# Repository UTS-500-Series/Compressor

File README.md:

# UTS Mini Mixing Desk — Compressor

A 500-series compressor module for the UTS Mini Mixing Desk. Feedback topology, discrete
current-steering gain cell, balanced in and out, running on the rack's ±16 V.

Built from ordinary parts: **nine BC549 transistors and seven NE5532 op amps**, plus a
pair of LM391x bargraph drivers for the meters. No VCA chip,
no transformers, nothing hard to source.

📖 **Documentation: [uts-500-series.github.io/compressor](https://uts-500-series.github.io/compressor/)** — every section explained, with
interactive schematics you can click through, plus the routed boards and their design files.
The site's source is a separate repository, [UTS-500-Series.github.io](https://github.com/UTS-500-Series/UTS-500-Series.github.io).

---

## Status

| | |
|---|---|
| Schematic | Complete, 7 sheets |
| Components | 166 |
| Nets | 110 |
| ERC | 0 errors, 0 warnings |
| PCB layout | Main board and front board placed and routed, DRC clean. Main board re-routed with paired audio lines and an unbroken ground pour; front board still as autorouted |
| Simulated | Yes, in ngspice from the `kicad/` sheets. See [kicad/sim](kicad/sim/README.md) |
| Built | No |

**Every performance figure in the documentation is calculated from the design, not measured.**
The netlist has been verified and ERC is clean, but that only proves the drawing is
self-consistent — not that the circuit behaves as predicted. The [simulation](kicad/sim/README.md)
checks the behaviour with models of the real parts, and found a few places where it differs
from the documentation.

## Repository layout

```
kicad_withpcb/compressor_with_pcb/   the main board: flat schematic + routed PCB (KiCad 10)
kicad_withpcb/compressor_front/      the front board behind the panel: schematic + routed PCB
kicad/                               the original seven-sheet schematic (KiCad 9), used by the site
tools/                               design.py (the reference netlist) and the check/build scripts
panel/                               faceplate generator — mockups, a 1:1 drawing and a DXF
```

**The boards are built from `kicad_withpcb/`.** The flat schematic there drives the main
board's PCB, and the front board has its own schematic joined to it by a 30-way ribbon.
`tools/design.py` is the reference netlist. Compare the flat schematic against it after any
wiring edit: KiCad's DRC parity check only compares the PCB with the flat schematic, so it
can't see a wiring mistake in the schematic itself.

The seven-sheet `kicad/` project is the original drawing of the same circuit. It has no PCB,
but the documentation site's interactive schematics are built from it. The site lives in its
own repository, [UTS-500-Series.github.io](https://github.com/UTS-500-Series/UTS-500-Series.github.io),
because it covers the whole desk rather than this module.

## Opening it

The boards need **KiCad 10**:

- `kicad_withpcb/compressor_with_pcb/compressor_with_pcb.kicad_pro`: the main board, the
  500-series card (152.35 × 105 mm) with the edge connector.
- `kicad_withpcb/compressor_front/compressor_front.kicad_pro`: the 35 × 110 mm front board
  with the pots, toggles and meters. Its [README](kicad_withpcb/compressor_front/README.md)
  covers how it mounts, the ribbon, the bracket and what to check before ordering.

Run `sh tools/get_3d_models.sh` once after cloning. It fetches Alps' RK09K pot model, which
isn't kept in git, so the 3D viewer and STEP export show the pots.

The original schematic is `kicad/UTS Mini Mixing Desk - Compressor.kicad_pro` (**KiCad 9**). Its root sheet holds seven
sub-sheets:

| Sheet | What it covers |
|---|---|
| 1 Connector | The 500-series edge connector |
| 2 Input | Balanced receiver and the input pad |
| 3 VCA | The current-steering gain cell and recovery amplifier |
| 4 Output | Makeup gain, output drivers, bypass, aux section |
| 5 Sidechain | Detector: threshold, rectifier, ratio, attack/release |
| 6 Power | Rails, references, bias, grounding, decoupling |
| 7 Meters | Gain-reduction and output-level LED bargraphs |

Only stock KiCad symbol and footprint libraries are used, so there is nothing to install.

## How it works, in one paragraph

A compressor needs a gain it can change electrically, and a way to measure loudness. The gain
cell here keeps a **fixed 3 mA tail current** through a matched BC549 pair and varies gain by
*steering* that current between an output load and the supply rail, rather than by varying the
current itself. That costs four extra transistors and buys a distortion figure that stays flat
at every amount of gain reduction — the simpler tail-current approach distorts worst exactly
when it is compressing hardest. The detector listens to the module's own **output**, making
this a feedback compressor: the ratio emerges from loop gain rather than being dialled in, the
knee comes out soft on its own, and the circuit is forgiving of component tolerance.

The [documentation](../UTS-500-Series.github.io) covers all of this properly, section by section.

## Specifications

| | |
|---|---|
| Format | 500 series, 15-pin EDAC card edge |
| Supply | ±16 V from the rack, 72 / 62 mA at rest (simulated) |
| Input | Balanced, 44 kΩ differential, +4 dBu nominal |
| Output | Balanced, 100 Ω build-out per leg |
| Gain reduction | 36 dB maximum (simulated) |
| Attack | 2 – 71 ms (simulated) |
| Release | 49 ms – 3.5 s (simulated) |
| Controls | Threshold, Ratio, Attack, Release, Makeup |
| Switches | Bypass, sidechain key int/ext, sidechain HPF, stereo link |

## Front panel

[`panel/`](panel/) holds the faceplate: a mockup, a dimensioned 1:1 drawing, and a DXF of the
outline and holes for a panel shop. All three are generated from one definition by
`panel/make_panel.py`, which runs a clearance check on every build.

Panel is the standard 500-series 1.500″ × 5.250″ × 0.125″ with two countersunk mounting holes
125.43 mm apart, badged **OPN-500 / CMP-01**.

The default layout, and the one the front board is built for, is **`toggle`**: five single
9 mm pots (THRESHOLD, RATIO, ATTACK, RELEASE, MAKEUP), four mini toggles (HPF and KEY
either side of THRESHOLD, LINK and BYPASS either side of RATIO), and two 10-LED meters for
gain reduction and output level. That's 31 holes, and `make_panel.py` takes their
positions from the front board. The toggles are Salecom mini toggles from Altronics:
S1350 (DPDT) for BYPASS and S1315 (SPDT) for KEY, HPF and LINK, in 6.5 mm holes for their
1/4-40 bushings. The S1332 (SPDT centre-off) fits the same footprint if a three-position
switch is ever wanted.

The toggles' 8.9 mm bushing leaves about 5.5 mm of thread through a 3.18 mm panel, so they
are no longer the tight spot. The 9 mm pots are: their 5 mm bushing leaves under 2 mm for
the nut, so thin the panel to about 2 mm around the five pot holes, or use a thinner panel.

`make_panel.py` also keeps a `pull` layout (every switch on a pull-switch pot) and a
`concentric` layout (dual-concentric knobs and a lit BYPASS button), plus a `bone` finish
alongside the default dark anodised one. The boards are only drawn for `toggle`. See
[`panel/README.md`](panel/README.md).

No laser cutter or CNC? [`panel/print/`](panel/print/README.md) has a 3D-printable faceplate
(STL and OpenSCAD) with the same holes, a flat front at the pots, meter holes sized for the
Jaycar 2 mm tower LEDs, an engraved legend that can print in a second colour, and a
fit-test strip to print first. It also comes
as a STEP file (`faceplate.step`) for Fusion or any other CAD program, plus a STEP with no
legend and the legend as a DXF, for laying out your own.

## Bill of materials

**[`bom/altronics.csv`](bom/altronics.csv)** is the order list for both boards from Altronics,
with catalogue codes, a link to each product page, pack sizes, prices and the stock their
site showed on the day it was checked. `python3 tools/bom_altronics.py` rebuilds it from the two `kicad_withpcb`
schematics, so it follows the boards rather than `design.py`; a part drawn on both sheets
is counted once, on the front board. It includes the hardware the schematics don't: DIP-8
sockets for U1–U7, knobs, the board-to-board ribbon and M3 screws for the bracket. The
two LM3914 meter drivers are soldered straight in, because sockets would overlap the
meter LEDs.

Altronics doesn't stock everything. The script lists those lines with another supplier:
the 2.2–10 µF film capacitors, R61/R62 at 0.1%, and the twenty 2 mm meter LEDs (Altronics'
3 mm flangeless LEDs don't fit the meters' 3.0 mm pitch). The main board is drawn for these
film capacitors: TDK B32562H1106K000 (10 µF, C5, C8, C15) and
B32562H1475K000 (4.7 µF, C9, C10), both 15 mm pitch, and KEMET MMK5225K63J06L4BULK
(2.2 µF, C14, C35) on 5 mm. RV5 (ATTACK) is 10k and RV6 (RELEASE) 1M, Altronics' nearest
9 mm values.

**[`bom/ordered.csv`](bom/ordered.csv)** is what was actually bought for the first build,
split between Altronics, DigiKey and Jaycar, with the supplier, order code, part, quantity and
link for every reference on both boards.

- **Altronics:** the pots, toggles, knobs, trimpots, sockets, headers, ribbon, small ceramics,
  electrolytics, 1N4148/1N4004 diodes, the GR LED and R37, R42 and R44.
- **DigiKey:** the 10 µF and 4.7 µF film capacitors (C5, C8, C15, C9, C10), R61/R62 at 0.1%,
  the NE5532s, the BC549Cs, the BZX79 zener, the 100 nF ceramics and the 22 µF bipolars (C1, C2).
- **Jaycar:** every other resistor (0.5 W mini metal film, which fits the 0.25 W outline), the
  TL072, both LM3914s, the twenty meter LEDs and C14/C35.

Three substitutions differ from the drawing. The meter LEDs are Jaycar 2 mm tower LEDs, orange
in the amber positions. C14 and C35 are 2.2 µF bipolar electrolytics (Jaycar RY6804), because
the 2.2 µF film part was out of stock everywhere we looked; neither is in the audio path. C1/C2 are
Panasonic ECE-A1VN220U (35 V, the 50 V parts don't fit the 6.3 mm outline). The bracket
hardware wasn't in any order.

The output-level meter was an LM3915, whose ten steps are 3 dB apart. Nobody stocks it any
more, so U10 is now an LM3914 like the gain-reduction meter, and both meters have ten LEDs on
a 3.0 mm pitch (they had seven on 3.5 mm). R92 is 4k7, so RV8 can set the top level LED at
+18 dBu. The LM3914's steps are even in volts, so the level LEDs light at about −2, +4, +7.5,
+10, +12, +13.6, +15, +16, +17 and +18 dBu: a 20 dB span with the finest steps near
clipping. With RV7 set for a 30 dB top LED, the gain-reduction LEDs light at about 2, 3, 5,
7, 10, 13, 17, 21, 26 and 30 dB. Both scales are simulated: see
[kicad/sim/README.md](kicad/sim/README.md#the-meters).
`tools/bom_order.py` is the older DigiKey list, built from `design.py`.

The circuit itself is 172 components across 58 distinct line items: 73 resistors, 39 capacitors, 21 LEDs,
9 transistors, 8 potentiometers, 8 diodes, 7 op amps, 4 switches, 2 display drivers,
1 connector.

Four things are not substitutable:

- **Q1/Q2 must be a matched pair, and Q6–Q9 a matched quad**, all glued together so they stay
  at the same temperature. The steering balance is set by base-emitter voltages differing by
  tens of millivolts, and those drift ~2 mV per °C.
- **R1–R4 and R21–R24 want 0.1%.** R1–R4 set input common-mode rejection; R21–R24 set how well
  the recovery amp rejects the gain cell's step, which is audible as thump on fast attacks.
- **R61 (1k33) and R62 (23k2) want 0.1%.** They set the gain cell's resting point.
- **C15 must be film.** An electrolytic's leakage is in the same league as the release current
  at long settings and will shorten your slowest release.

One recommended deviation: fit a **TL072 or OPA2134 for U4** instead of an NE5532. Its inputs
sit on the timing capacitor, and the NE5532's ~200 nA bias current can leave the compressor
holding about a decibel of gain reduction at idle. Pin compatible, nothing else changes.

## Ordering the boards

Each board's fab files are in its `Gerbs/` folder, zipped ready to upload:
`kicad_withpcb/compressor_with_pcb/Gerbs/compressor_with_pcb-gerbers.zip` (main board,
128.4 × 105.05 mm including the edge-connector tab) and
`kicad_withpcb/compressor_front/Gerbs/compressor_front-gerbers.zip` (front board, 35 × 110 mm).
Both are 2-layer, 1.6 mm FR-4, 1 oz copper, through-hole only (no paste layers). Smallest
track 0.2 mm, clearance 0.2 mm, drill 0.4 mm, so any standard fab process takes them.

The main board's edge fingers plug into the rack, so ask for gold fingers with a 30–45° bevel
if the fab offers it. Plain HASL works for a prototype but wears with repeated insertion.

**Re-plot after every board change**, so the zips never lag the board:

```bash
sh tools/plot_fab.sh                 # both boards, needs KiCad 10's kicad-cli
```

## Calibrating the meters

`tools/calibrate_meters.py` sets RV8 (level) and RV7 (gain reduction) with an audio interface,
a loopback cable and a multimeter. It learns the interface's levels in dBu, then holds a tone
at each meter's target while you turn the trimpot, and can sweep each meter afterwards to check
every LED against the simulated scale in [kicad/sim/README.md](kicad/sim/README.md#the-meters).

```bash
python3 -m venv ~/meter-venv          # macOS/Homebrew Python refuses a system-wide pip install
source ~/meter-venv/bin/activate      # again in each new terminal
python3 -m pip install numpy sounddevice
python3 tools/calibrate_meters.py --list
python3 tools/calibrate_meters.py --device "<interface name>" --out 1 --in 1
```

The level meter is set at the top green LED (D34, +12.0 dBu out) and the gain-reduction meter
at the seventh LED from the top (D26, 16.7 dB), both reachable with an ordinary line input.
The loopback can also be a TRS-to-XLR cable into the XLR side of a combo input (gain at
minimum, phantom power off). A mic input clips lower, so the script checks its headroom and
sets the level meter at a lower LED if it has to (`--level-led` and `--gr-led` pick one by hand).

## Documentation site

The site is a **separate repository**, checked out beside this one as `../UTS-500-Series.github.io`. It covers
every module in the desk — compressor, preamp and equaliser — so it does not belong to any
one of them. It also owns its own GitHub Pages workflow.

The compressor's pages are interactive: pan and zoom the real schematic, click any part for
its value, footprint and nets, click a net to highlight everything on it, or switch to a
graph view of the netlist.

The site commits its generated data, so it builds and publishes without this repository
present. It only needs this one checked out when the schematic changes — see below.

## Tooling

Everything needed to check and rebuild the project lives in [`tools/`](tools/) — standard
library only, no packages to install. KiCad's paths are found automatically; override with
`KICAD_CLI` and `KICAD_SYMBOL_DIR` if yours are somewhere unusual.

```bash
python3 tools/verify_netlist.py      # check the schematic against design.py
sh tools/plot_fab.sh                 # plot Gerbers + drill files for both boards
```

`tools/gen_project.py` and `tools/route_sch.py` **regenerate the schematic from scratch and
will overwrite hand-drawn layout.** They built the first version; the sheets have been laid out
by hand since. See [`tools/README.md`](tools/README.md) before running either.

## How the schematic is verified

`tools/design.py` holds the netlist as data and is treated as the source of truth.
`tools/verify_netlist.py` exports the netlist from the schematic with `kicad-cli` and diffs it
against that definition **net by net and pin by pin**.

That is what catches the failure mode ERC cannot see: a wire dragged so its endpoint lands on a
neighbouring node shorts two signal nets together, and ERC reports nothing, because every pin
is still connected to *something*. Two such shorts were caught and fixed this way during layout
cleanup. Worth running after any significant edit — it takes a second and prints the exact nets
and pins involved when something is wrong.

## Regenerating the documentation

After changing a sheet, from the **docs** repository beside this one:

```bash
# 1. re-export the sheet images
kicad-cli sch export svg --no-background-color --exclude-drawing-sheet -o /tmp/svg \
  "kicad/UTS Mini Mixing Desk - Compressor.kicad_sch"
#    copy the seven sheets into ../UTS-500-Series.github.io/site/compressor/img/ as connector.svg, input.svg,
#    vca.svg, output.svg, sidechain.svg, power.svg, meters.svg

cd ../UTS-500-Series.github.io
python3 build/_data.py --module compressor   # hotspots + netlist graph, read from kicad/
python3 build/build_site.py                  # every page, every module
```

Both scripts import from `tools/`, so a fresh clone has everything it needs.

## Known gaps

- **The main board was re-routed by script, not by hand, so look it over in KiCad before
  ordering.** IN± and OUT± now run as pairs 0.6 mm apart on the top layer, with one via each
  on IN− and OUT− beside the edge fingers. Nearly everything else moved to the top so the AGND
  pour on the bottom is one piece (it was seven, one of them cut off near the fingers). The cost
  is more vias: 155, up from 37. The timing node (C15, U4, D7, J2) is 44 mm, about as short as
  the placement allows; shortening it further means moving C15.
- **The front board's tracks are still as the autorouter left them**, with its ground pour in
  12 pieces. It carries the bypass switch's IN± and OUT± runs, so tidy those if anything.
- **Check one toggle and one pot against their footprints before ordering boards.** The
  Salecom footprints follow the drawings on Altronics' product pages; Altronics doesn't
  dimension where the 9 mm pot's shaft sits relative to its lugs, so confirm it lines up
  with the panel hole.
- **Check the mechanics in a real rack:** the front board now sits about 10.6 mm behind the
  panel (the pots' body height; the toggles stand 10.4 mm), the panel thickness at the pots,
  the ribbon length (about 150 mm is an estimate), and that the ribbon plug on J1 still
  clears the main board's front edge, 24 mm back.
- **The main board was re-placed and re-routed by script to fit the full-size film
  capacitors.** The film caps went in near their old spots, 56 resistors, small caps and
  diodes moved or swapped places to make room (transistors, ICs, connectors and trimmers
  stayed put), and the whole board was re-routed by script (see the item above). Keep the
  timing node (C15, U4) and the recovery-amp inputs (C9, C10, R21, R22, U1) short if you
  move anything.
- Pin 11 is used as an auxiliary input, which the API 500 specification assigns to a gain-trim
  node. The aux section (U5 and its resistors) is a separable block; omit it and the module is
  fully standards-compliant.
- Simulated in ngspice only (see [kicad/sim](kicad/sim/README.md)): no instability at the
  fastest attack and hardest ratio there, but the op amp model is behavioural, so check on the bench.

## Licence

Copyright 2026 the UTS 500 Series team.

This source describes Open Hardware and is licensed under the CERN-OHL-S v2.

You may redistribute and modify this source and make products using it under
the terms of the [CERN-OHL-S v2](https://ohwr.org/cern_ohl_s_v2.txt).

This source is distributed WITHOUT ANY EXPRESS OR IMPLIED WARRANTY, INCLUDING
OF MERCHANTABILITY, SATISFACTORY QUALITY AND FITNESS FOR A PARTICULAR PURPOSE.
Please see the CERN-OHL-S v2 for applicable conditions.

Source location: https://github.com/UTS-500-Series/Compressor

As per CERN-OHL-S v2 section 4, should You produce hardware based on this
source, You must where practicable maintain the Source Location visible on the
external case of the compressor module or other products you make
using this source.

The full licence text is in [LICENSE](LICENSE).

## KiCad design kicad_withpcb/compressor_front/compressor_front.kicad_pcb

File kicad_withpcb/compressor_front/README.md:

# Compressor front board

A 35 × 110 mm board that sits flat behind the faceplate and carries everything on the
panel: the five pots, the four toggles, and both LED meters with their two LM3914
drivers. It joins the main board with a 30-way ribbon from J1 here to J2 on the main board,
pin for pin, with the same net names in both schematics.

The parts are the ones drawn in the main schematic. They stay drawn there (excluded from
that board and its BOM) so the circuit still reads as one piece.

## How it sits

- The front of the board faces the panel. Pots, toggles, LEDs, the driver ICs and their
  small parts all go on the front.
- J1 (a plain 2×15 pin header) and C38 (47 µF, too tall for the front) go on the back.
- The toggles are Salecom mini toggles from Altronics: S1350 (DPDT) for BYPASS, S1315 (SPDT)
  for KEY, HPF and LINK. Their body stands 10.4 mm off the board and the Altronics 9 mm pots
  stand 10.6 mm, so the board sits **about 10.6 mm behind the panel**, with the pot bodies
  against the back of the panel and the toggles 0.2 mm short of it.
- Alps RK09K pots, if you use them instead, are shorter: make up the difference with a nut
  behind the panel, which may need the longer bushing version.
- The LEDs need spacers to reach the panel: about 7.8 mm for the 2 mm flat-tops drawn here
  (10.6 mm gap less the 2.8 mm LED).
- Each meter is a column of ten LEDs on a 3.0 mm pitch, so the LED bodies are 0.2 mm apart.
  The LED footprints' courtyards and silkscreen are trimmed to suit (DRC lists them as
  differing from the library). 3 mm LEDs no longer fit.
- The pots' 5 mm bushing leaves under 2 mm of thread through a 3.18 mm panel: see
  `panel/README.md` on panel thickness. The toggles' 8.9 mm bushing is plenty.
- The pins of all four toggles come through the back by about 0.8 mm.
- The main board's front edge is set back 24 mm from the panel to clear this board, the
  header and the ribbon plug. The board's back face is now about 12.2 mm behind the panel,
  so check the plug on J1 still clears it, especially with single-way sockets (taller than
  an IDC plug).

## Joining the boards

The boards are joined only by the ribbon; each one is fixed to the faceplate on its own.

- **Ribbon:** 30-way, 2.54 mm pitch, with an IDC socket crimped on each end. Main board
  J2 is a shrouded box header; J1 here is a plain pin header, so it isn't keyed. Put the
  red stripe on pin 1 at both ends (pin 1 is marked on the back silkscreen).
  Altronics has no 30-way IDC parts, so `bom/altronics.csv` lists a plain 2×15 header for
  J2 as well and a 150 mm socket-to-socket strip of single-way leads (P1023) for the ribbon.
  It works, but nothing keys it: keep lead 1 on pin 1 at both ends. For a proper IDC ribbon,
  buy the box header, two sockets and cable from element14.
- **Length:** about 150 mm, folded once between the boards. J2 sits roughly 30 mm behind
  the panel and about 35 mm higher than J1, and the sideways distance depends on where the
  main board sits in your rack, so lay the boards out and check before crimping.
- **Front board to panel:** the nuts on the five pot and four toggle bushings.
- **Main board to panel:** an L-bracket from the back of the panel to H1 and H2, the two
  M3 holes by the main board's front edge (85 mm apart). The front edge is 24 mm behind
  the panel, so the bracket leg along the board needs to reach that far: 25 × 25 mm
  aluminium angle, or a short angle with standoffs. H2 is plated and tied to CHASSIS
  (J1 pin 1), so the bracket also grounds the panel as the faceplate guide asks. Mask
  the anodise where the bracket touches the panel.
  The 3D-printed faceplate in `panel/print/` has this bracket built in: two ears that
  H1 and H2 screw to with M3 × 6 screws into captive nuts, and a wall that runs back
  along the main board to cover its solder side.

## Coordinates

The panel outline and every hole are drawn on User.Drawings, with the grid origin on the
panel's top-left corner. The board editor's coordinates read the same as the panel
drawing, and `panel/make_panel.py` takes its hole positions from this board.

## 3D models

Every part has a 3D model, so the 3D viewer and a STEP export (for the Fusion 360 assembly)
show both boards complete.

- Most come from KiCad's own library.
- The pots use Alps' official RK09K1130 model. It's the maker's file, so it isn't kept in
  git: run `sh tools/get_3d_models.sh` once to fetch it into `3dmodels/`. The pots use a
  project copy of the stock RK09K footprint that points at it.
- The toggles use simple models built to the Altronics drawings by
  `tools/make_toggle_models.py` (case, bushing, lever and pins).
- The main board's edge fingers are copper, not a part, so J1 there has no model.

## Check before ordering

- **The toggle footprints follow the drawings on Altronics' S1315 and S1350 pages:** pins on
  4.70 mm, 1.3 mm holes, the DPDT's two rows 4.83 mm apart. The S1332 (centre off) has the
  same drawing as the S1315, so it drops into any SPDT position. Check one switch against the
  footprint before ordering boards.
- The toggles sit at x = 7.15 and 30.95 mm (panel coordinates), 0.25 mm in from the old
  sub-miniature positions, so the S1350's 11.4 mm body stays on the board. The pot footprint's
  courtyard was trimmed to its pads so it doesn't overlap the S1350's.
- **The Altronics 9 mm pots (R19xx)** have the RK09K's pin and lug pattern (lugs 8.6 mm apart,
  pins 7.0 mm behind them), so they use the same footprint. Their drawing doesn't place the
  shaft relative to the lugs; the RK09K's is 0.5 mm beyond them. Check before cutting the panel.
- SW3 (HPF) and SW4 (LINK) are single-pole in the schematic and use the SPDT footprint's
  top and centre pins; the bottom pin is unused.
- There are no mounting holes: the nine bushing nuts hold the board. Add standoffs if it
  flexes.

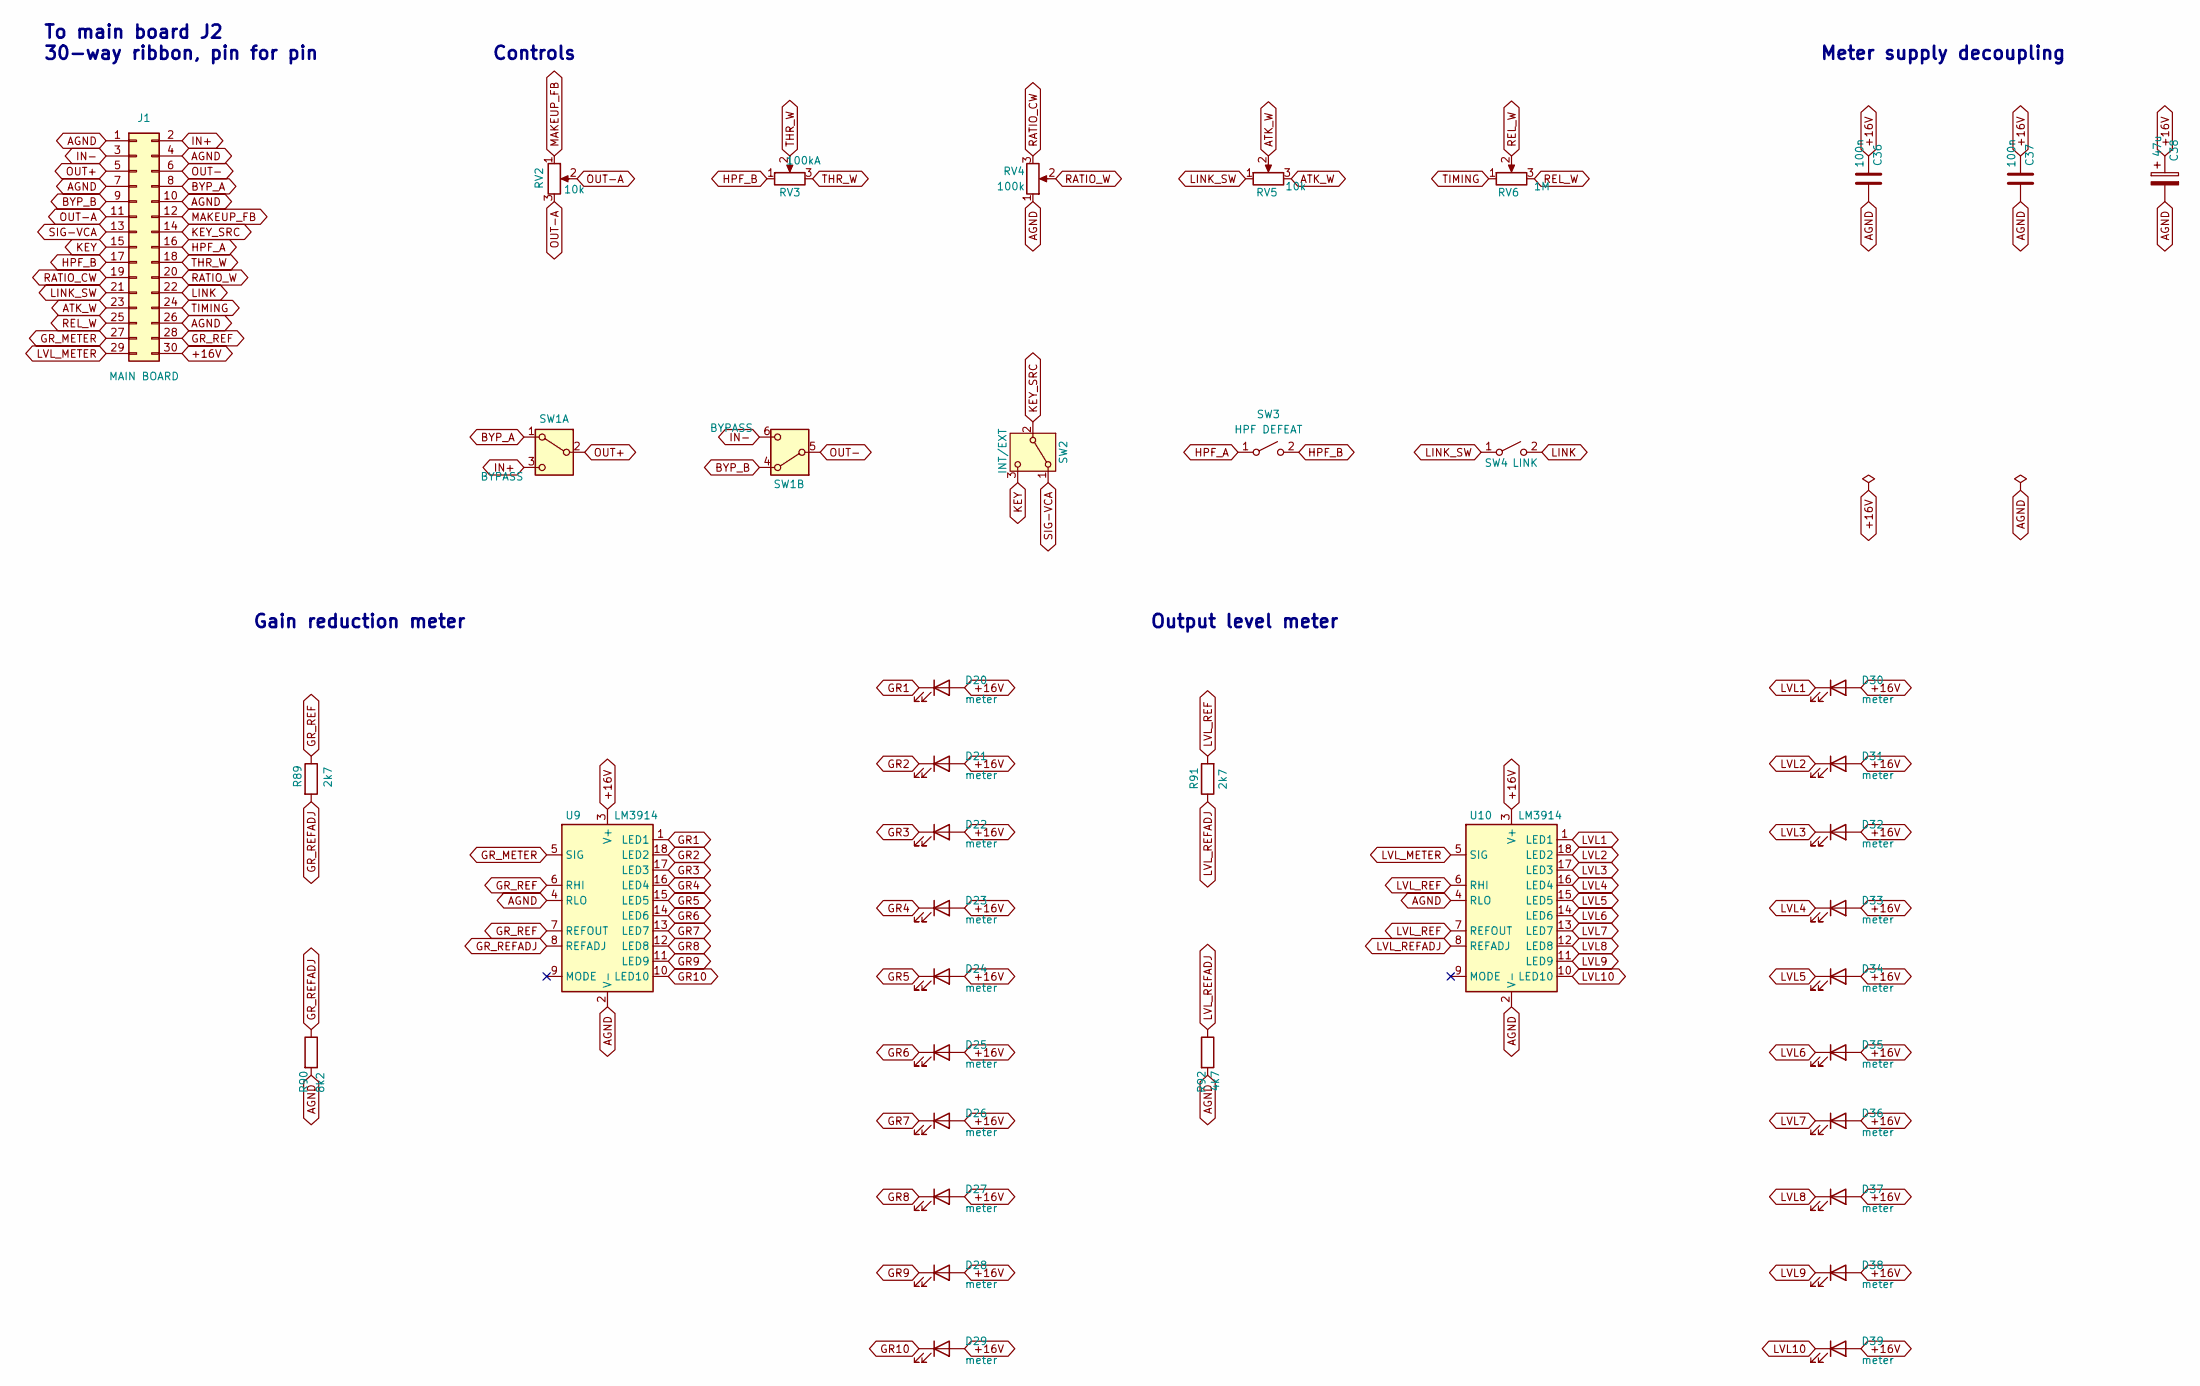
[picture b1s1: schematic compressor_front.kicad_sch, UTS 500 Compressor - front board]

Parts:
C36, C37: 100n; C_Disc_D5.0mm_W2.5mm_P5.00mm
C38: 47u; CP_Radial_D6.3mm_P2.50mm
D20, D21, D22, D23, D24, D25, D26, D27, D28, D29, D30, D31, D32, D33, D34, D35, D36, D37, D38, D39: meter; LED_D2.0mm_W4.0mm_H2.8mm_FlatTop
J1: MAIN BOARD; PinHeader_2x15_P2.54mm_Vertical
R89, R91: 2k7; R_Axial_DIN0207_L6.3mm_D2.5mm_P10.16mm_Horizontal
R90: 8k2; R_Axial_DIN0207_L6.3mm_D2.5mm_P7.62mm_Horizontal
R92: 4k7; R_Axial_DIN0207_L6.3mm_D2.5mm_P7.62mm_Horizontal
RV2, RV5: 10k; Potentiometer_Alps_RK09K_Single_Vertical
RV3: 100kA; Potentiometer_Alps_RK09K_Single_Vertical
RV4: 100k; Potentiometer_Alps_RK09K_Single_Vertical
RV6: 1M; Potentiometer_Alps_RK09K_Single_Vertical
SW1: BYPASS; SW_Toggle_Mini_DPDT_Salecom_S1350
SW2: INT/EXT; SW_Toggle_Mini_SPDT_Salecom_S1315
SW3: HPF DEFEAT; SW_Toggle_Mini_SPDT_Salecom_S1315
SW4: LINK; SW_Toggle_Mini_SPDT_Salecom_S1315
U9, U10: LM3914; DIP-18_W7.62mm

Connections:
+16V: C36.1, C37.1, C38.1, D20.2 (A), D21.2 (A), D22.2 (A), D23.2 (A), D24.2 (A), D25.2 (A), D26.2 (A), D27.2 (A), D28.2 (A), D29.2 (A), D30.2 (A), D31.2 (A), D32.2 (A), D33.2 (A), D34.2 (A), D35.2 (A), D36.2 (A), D37.2 (A), D38.2 (A), D39.2 (A), J1.30, U9.3 (V+), U10.3 (V+)
AGND: C36.2, C37.2, C38.2, J1.1, J1.4, J1.7, J1.10, J1.26, R90.2, R92.2, RV4.1, U9.2 (V-), U9.4 (RLO), U10.2 (V-), U10.4 (RLO)
ATK_W: J1.23, RV5.2, RV5.3
BYP_A: J1.8, SW1.1 (A)
BYP_B: J1.9, SW1.4 (A)
GR1: D20.1 (K), U9.1 (LED1)
GR2: D21.1 (K), U9.18 (LED2)
GR3: D22.1 (K), U9.17 (LED3)
GR4: D23.1 (K), U9.16 (LED4)
GR5: D24.1 (K), U9.15 (LED5)
GR6: D25.1 (K), U9.14 (LED6)
GR7: D26.1 (K), U9.13 (LED7)
GR8: D27.1 (K), U9.12 (LED8)
GR9: D28.1 (K), U9.11 (LED9)
GR10: D29.1 (K), U9.10 (LED10)
GR_METER: J1.27, U9.5 (SIG)
GR_REF: J1.28, R89.1, U9.6 (RHI), U9.7 (REFOUT)
GR_REFADJ: R89.2, R90.1, U9.8 (REFADJ)
HPF_A: J1.16, SW3.1 (A)
HPF_B: J1.17, RV3.1, SW3.2 (B)
IN+: J1.2, SW1.3 (C)
IN-: J1.3, SW1.6 (C)
KEY: J1.15, SW2.3 (C)
KEY_SRC: J1.14, SW2.2 (B)
LINK: J1.22, SW4.2 (B)
LINK_SW: J1.21, RV5.1, SW4.1 (A)
LVL1: D30.1 (K), U10.1 (LED1)
LVL2: D31.1 (K), U10.18 (LED2)
LVL3: D32.1 (K), U10.17 (LED3)
LVL4: D33.1 (K), U10.16 (LED4)
LVL5: D34.1 (K), U10.15 (LED5)
LVL6: D35.1 (K), U10.14 (LED6)
LVL7: D36.1 (K), U10.13 (LED7)
LVL8: D37.1 (K), U10.12 (LED8)
LVL9: D38.1 (K), U10.11 (LED9)
LVL10: D39.1 (K), U10.10 (LED10)
LVL_METER: J1.29, U10.5 (SIG)
LVL_REF: R91.2, U10.6 (RHI), U10.7 (REFOUT)
LVL_REFADJ: R91.1, R92.1, U10.8 (REFADJ)
MAKEUP_FB: J1.12, RV2.1
OUT+: J1.5, SW1.2 (B)
OUT-: J1.6, SW1.5 (B)
OUT-A: J1.11, RV2.2, RV2.3
RATIO_CW: J1.19, RV4.3
RATIO_W: J1.20, RV4.2
REL_W: J1.25, RV6.2, RV6.3
SIG-VCA: J1.13, SW2.1 (A)
THR_W: J1.18, RV3.2, RV3.3
TIMING: J1.24, RV6.1

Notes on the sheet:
To main board J2 30-way ribbon, pin for pin
Controls
Gain reduction meter
Output level meter
Meter supply decoupling

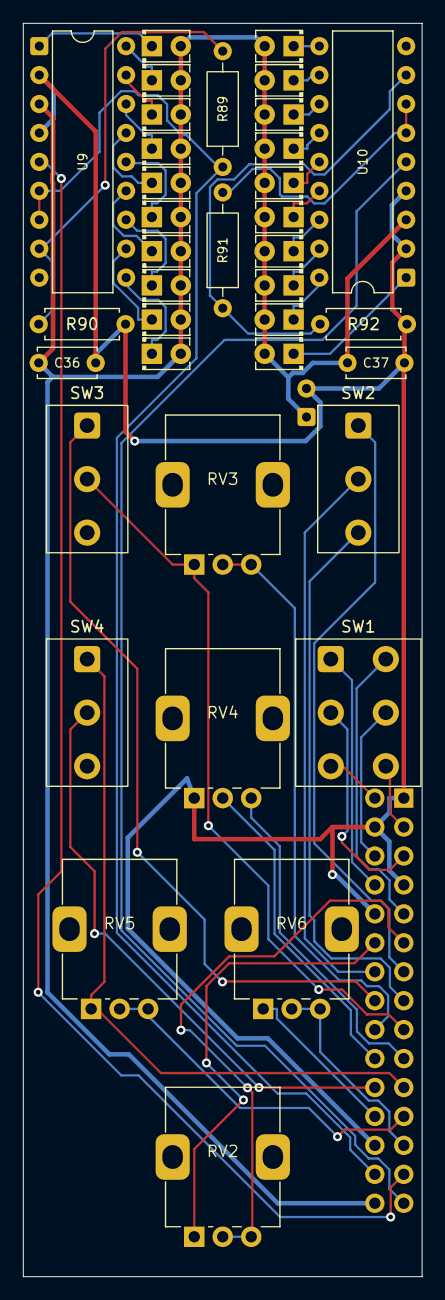
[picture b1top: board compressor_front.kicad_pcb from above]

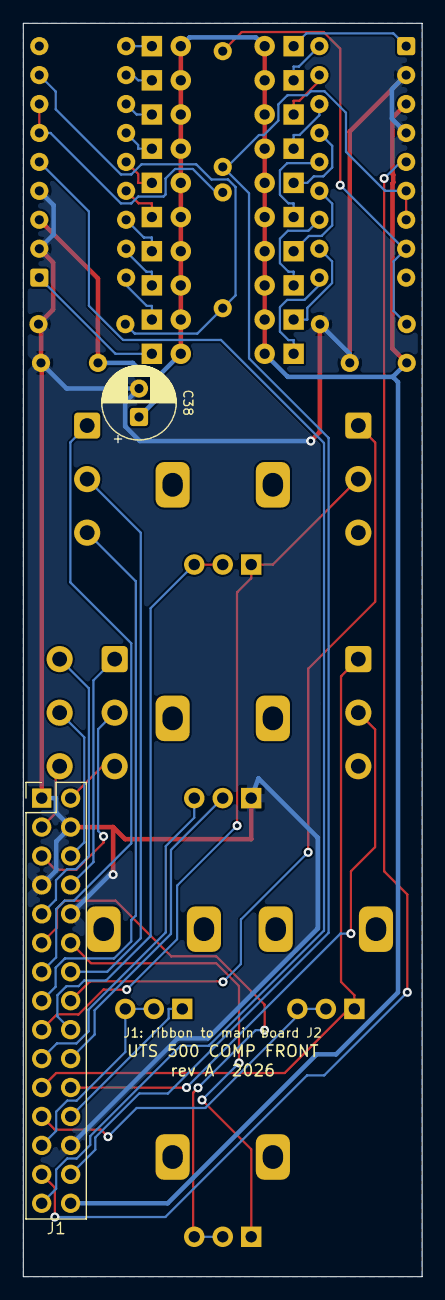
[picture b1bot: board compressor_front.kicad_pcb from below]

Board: 2 copper layers, 35.0 x 110.0 mm, 39 parts (2 on the bottom side), 49 nets.

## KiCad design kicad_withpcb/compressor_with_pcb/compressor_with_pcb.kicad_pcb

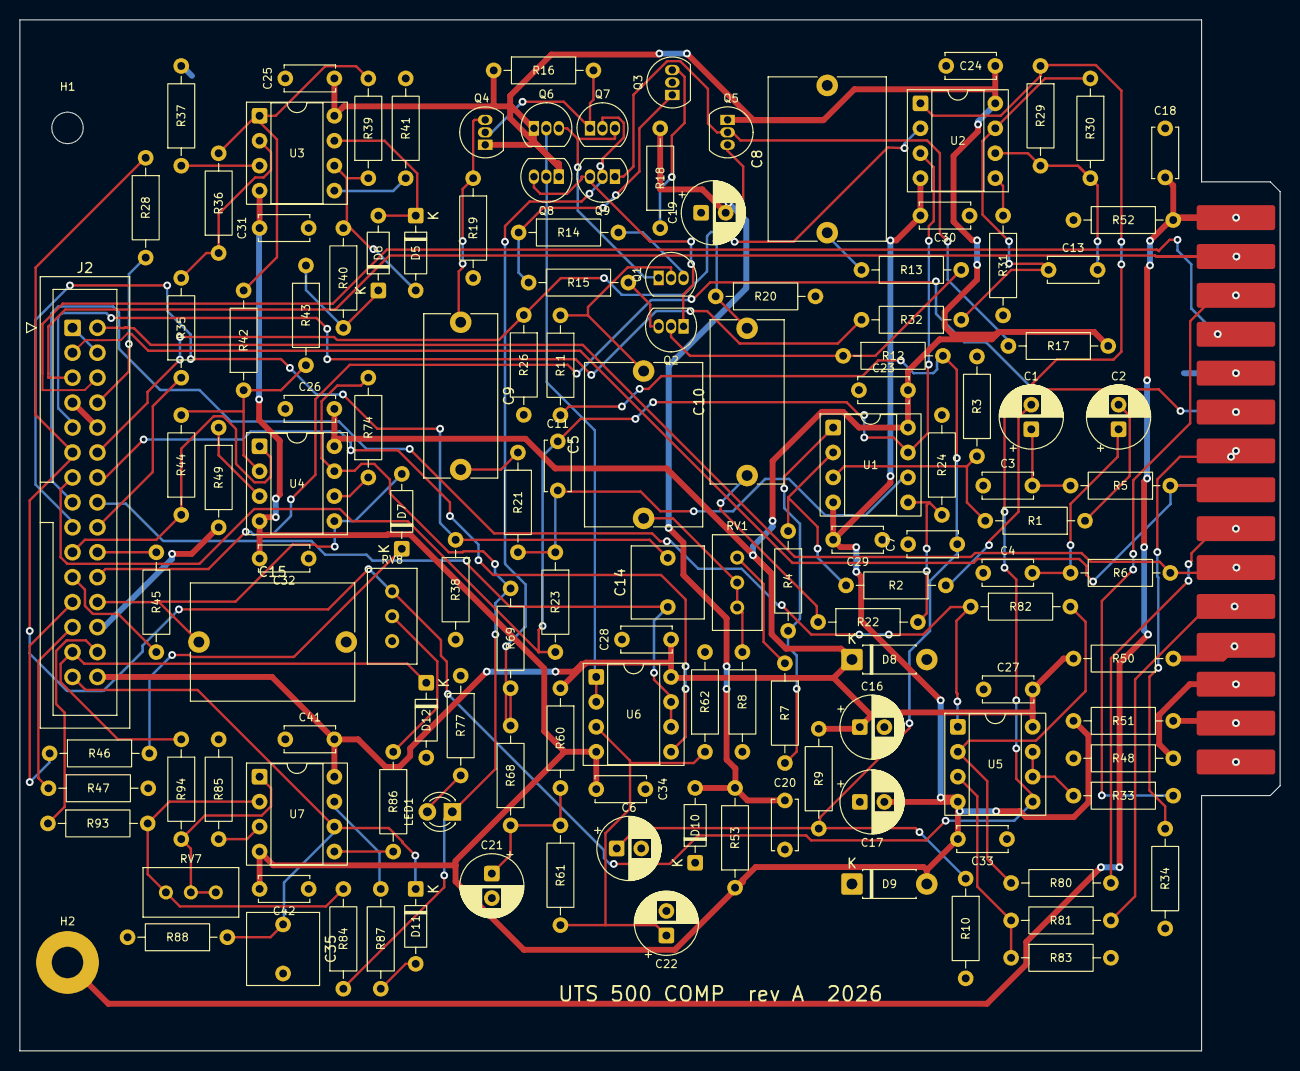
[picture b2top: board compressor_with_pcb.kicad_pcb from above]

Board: 2 copper layers, 128.3 x 105.0 mm, 137 parts (0 on the bottom side), 93 nets.

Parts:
C1, C2: 22u; CP_Radial_D6.3mm_P2.50mm
C3, C4: 1n; C_Disc_D5.0mm_W2.5mm_P5.00mm
C5, C8, C15: 10u; C_Rect_L16.5mm_W11.8mm_P15.00mm_MKT
C6, C16, C17: 100u; CP_Radial_D6.3mm_P2.50mm
C7, C20, C23, C24, C25, C26, C27, C28, C29, C30, C31, C32, C33, C34, C41, C42: 100n; C_Disc_D5.0mm_W2.5mm_P5.00mm
C9, C10: 4u7; C_Rect_L16.5mm_W7.3mm_P15.00mm_MKT
C11, C13: 100p; C_Disc_D5.0mm_W2.5mm_P5.00mm
C14, C35: 2u2; C_Rect_L7.2mm_W7.2mm_P5.00mm_FKS2_FKP2_MKS2_MKP2
C18: 10n; C_Disc_D5.0mm_W2.5mm_P5.00mm
C19, C21: 47u; CP_Radial_D6.3mm_P2.50mm
C22: 4u7; CP_Radial_D6.3mm_P2.50mm
D5, D6, D7, D11, D12: 1N4148; D_DO-35_SOD27_P7.62mm_Horizontal
D8, D9: 1N4004; D_DO-41_SOD81_P7.62mm_Horizontal
D10: BZX79-C5V1; D_DO-35_SOD27_P7.62mm_Horizontal
H1: Bracket M3; MountingHole_3.2mm_M3
H2: Bracket M3; MountingHole_3.2mm_M3_Pad
J1: EDA 306; EDA_306
J2: FRONT BOARD; IDC-Header_2x15_P2.54mm_Vertical
LED1: GR; LED_D3.0mm
Q1, Q2, Q3, Q4, Q5, Q6, Q7, Q8, Q9: BC549C; TO-92_Inline
R1, R2, R3, R4, R23, R24, R80, R81, R82, R83: 22k; R_Axial_DIN0207_L6.3mm_D2.5mm_P10.16mm_Horizontal
R5, R6, R28, R32, R33, R34, R52: 100R; R_Axial_DIN0207_L6.3mm_D2.5mm_P10.16mm_Horizontal
R7: 8k2; R_Axial_DIN0207_L6.3mm_D2.5mm_P10.16mm_Horizontal
R8: 75R; R_Axial_DIN0207_L6.3mm_D2.5mm_P10.16mm_Horizontal
R9: 68k; R_Axial_DIN0207_L6.3mm_D2.5mm_P10.16mm_Horizontal
R10: 11k; R_Axial_DIN0207_L6.3mm_D2.5mm_P10.16mm_Horizontal
R11, R12, R19, R20, R29, R30, R39, R40, R41, R43, R84, R85, R86, R94: 10k; R_Axial_DIN0207_L6.3mm_D2.5mm_P10.16mm_Horizontal
R13, R14, R15, R45: 220R; R_Axial_DIN0207_L6.3mm_D2.5mm_P10.16mm_Horizontal
R16, R17: 4k7; R_Axial_DIN0207_L6.3mm_D2.5mm_P10.16mm_Horizontal
R18: 1k5; R_Axial_DIN0207_L6.3mm_D2.5mm_P10.16mm_Horizontal
R21, R22: 6k8; R_Axial_DIN0207_L6.3mm_D2.5mm_P10.16mm_Horizontal
R26, R35, R38, R68, R87: 1k; R_Axial_DIN0207_L6.3mm_D2.5mm_P10.16mm_Horizontal
R31, R49: 5k1; R_Axial_DIN0207_L6.3mm_D2.5mm_P10.16mm_Horizontal
R36: 82k; R_Axial_DIN0207_L6.3mm_D2.5mm_P10.16mm_Horizontal
R37: 47k; R_Axial_DIN0207_L6.3mm_D2.5mm_P10.16mm_Horizontal
R42, R44: 20k; R_Axial_DIN0207_L6.3mm_D2.5mm_P10.16mm_Horizontal
R46: 47R; R_Axial_DIN0207_L6.3mm_D2.5mm_P10.16mm_Horizontal
R47: 15k; R_Axial_DIN0207_L6.3mm_D2.5mm_P10.16mm_Horizontal
R48: 0R; R_Axial_DIN0207_L6.3mm_D2.5mm_P10.16mm_Horizontal
R50, R51: 10R; R_Axial_DIN0207_L6.3mm_D2.5mm_P10.16mm_Horizontal
R53: 1k8; R_Axial_DIN0207_L6.3mm_D2.5mm_P10.16mm_Horizontal
R60: 24k; R_Axial_DIN0207_L6.3mm_D2.5mm_P10.16mm_Horizontal
R61: 1k33; R_Axial_DIN0207_L6.3mm_D2.5mm_P10.16mm_Horizontal
R62: 23k2; R_Axial_DIN0207_L6.3mm_D2.5mm_P10.16mm_Horizontal
R69: 36k; R_Axial_DIN0207_L6.3mm_D2.5mm_P10.16mm_Horizontal
R74: 220k; R_Axial_DIN0207_L6.3mm_D2.5mm_P10.16mm_Horizontal
R77: 3k9; R_Axial_DIN0207_L6.3mm_D2.5mm_P10.16mm_Horizontal
R88: 100k; R_Axial_DIN0207_L6.3mm_D2.5mm_P10.16mm_Horizontal
R93: 18k; R_Axial_DIN0207_L6.3mm_D2.5mm_P10.16mm_Horizontal
RV1: 2k; Potentiometer_Bourns_3296W_Vertical
RV7, RV8: 20k; Potentiometer_Bourns_3296W_Vertical
U1, U2, U3, U5, U6, U7: NE5532; DIP-8_W7.62mm_Socket
U4: TL072; DIP-8_W7.62mm_Socket

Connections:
+16V: C16.1, C23.1, C24.1, C25.1, C26.1, C27.1, C28.1, C41.1, D8.1 (K), J2.30, Q4.1 (C), Q5.1 (C), Q6.1 (C), Q8.1 (C), R9.2, R16.1, R17.1, R50.2, R60.1, U1.8 (V+), U2.8 (V+), U3.8 (V+), U4.8 (V+), U5.8 (V+), U6.8 (V+), U7.8 (V+)
+16V-IN: J1.12, R50.1
-5V1: C19.2, C20.1, D10.2 (A), R18.2, R53.2
-16V: C17.2, C29.1, C30.1, C31.1, C32.1, C33.1, C34.1, C42.1, D9.2 (A), R51.2, R53.1, U1.4 (V-), U2.4 (V-), U3.4 (V-), U4.4 (V-), U5.4 (V-), U6.4 (V-), U7.4 (V-)
-16V-IN: J1.14, R51.1
AGND: C3.2, C4.2, C6.2, C7.2, C8.2, C15.2, C16.2, C17.1, C18.2, C19.1, C20.2, C21.2, C22.2, C23.2, C24.2, C25.2, C26.2, C27.2, C28.2, C29.2, C30.2, C31.2, C32.2, C33.2, C34.2, C35.2, C41.2, C42.2, D8.2 (A), D9.1 (K), D10.1 (K), D12.2 (A), J1.5, J2.1, J2.4, J2.7, J2.10, J2.26, Q3.2 (B), R3.2, R8.2, R10.2, R19.2, R20.2, R24.2, R26.2, R31.2, R34.1, R37.2, R38.2, R41.2, R47.2, R48.2, R49.2, R52.2, R62.2, R77.1, R83.2, R85.2, R88.2, RV8.3
ATK_W: J2.23, R46.1
AUXIN+: J1.11, R81.1
AUXIN-: J1.9, R80.1
AUXOUT+: J1.3, R33.2
AUXOUT-: J1.7, R34.2
BYP_A: J2.8, R28.2
BYP_B: J2.9, R32.2
CHASSIS: C18.1, H2.1, J1.1, R52.1
CTRL-B: LED1.1 (K), R69.2, R74.2, R84.1, U4.7
GR_METER: D12.1 (K), J2.27, R94.1
GR_REF: J2.28, R93.1
HPF_A: C14.1, J2.16, U6.6 (-), U6.7
HPF_B: C14.2, J2.17, R38.1
IN+: J1.10, J2.2, R6.1
IN-: J1.8, J2.3, R5.1
KEY: J2.15, R82.1, U5.1
KEY_SRC: J2.14, U6.5 (+)
LINK: J1.6, J2.22
LINK_SW: J2.21, R45.2
LVL_METER: C35.1, D11.1 (K), J2.29, R88.1, U7.6 (-)
MAKEUP_FB: J2.12, R26.1, U2.2 (-)
unnamed: C1.1, C3.1, R5.2
unnamed: C1.2, R2.1
unnamed: C2.1, C4.1, R6.2
unnamed: C2.2, R1.1
unnamed: C8.1, R13.2
unnamed: C9.2, R21.1
unnamed: C10.1, R22.1
unnamed: C13.1, R30.1, R32.1, U2.7
unnamed: C21.1, R60.2, R61.1, R68.1
unnamed: D5.2 (A), R39.1, R40.1, U3.6 (-)
unnamed: D5.1 (K), D6.2 (A), U3.7
unnamed: D6.1 (K), R40.2, R43.1
unnamed: D7.1 (K), R46.2
unnamed: D11.2 (A), R87.1
unnamed: LED1.2 (A), R77.2
unnamed: C5.2, Q1.2 (B), R11.1
unnamed: Q1.1 (C), Q6.3 (E), Q7.3 (E)
unnamed: Q1.3 (E), R14.2
unnamed: Q2.2 (B), R12.1, R13.1
unnamed: Q2.1 (C), Q8.3 (E), Q9.3 (E)
unnamed: Q2.3 (E), R15.1
unnamed: Q3.1 (C), R14.1, R15.2
unnamed: Q3.3 (E), R18.1
unnamed: Q4.2 (B), Q7.1 (C), R16.2
unnamed: C9.1, Q4.3 (E), R19.1
unnamed: Q5.2 (B), Q9.1 (C), R17.2
unnamed: C10.2, Q5.3 (E), R20.1
unnamed: R4.2, R7.2, U1.1
unnamed: R7.1, RV1.1
unnamed: R36.2, R39.2, R42.2, U3.1
unnamed: R86.1, RV8.2
unnamed: R87.2, U7.7
unnamed: R94.2, RV7.2, RV7.3, U7.1
unnamed: R1.2, R3.1, U1.3 (+)
unnamed: R2.2, R4.1, U1.2 (-)
unnamed: R22.2, R24.1, U1.5 (+)
unnamed: C11.1, R21.2, R23.1, U1.6 (-)
unnamed: R31.1, U2.5 (+)
unnamed: C13.2, R29.2, R30.2, U2.6 (-)
unnamed: R37.1, U3.3 (+)
unnamed: R35.2, R36.1, U3.2 (-)
unnamed: R41.1, U3.5 (+)
unnamed: R49.1, U4.3 (+)
unnamed: R42.1, R43.2, R44.2, U4.2 (-)
unnamed: R74.1, U4.6 (-)
unnamed: R81.2, R83.1, U5.3 (+)
unnamed: R80.2, R82.2, U5.2 (-)
unnamed: R33.1, U5.6 (-), U5.7
unnamed: C22.1, R61.2, R62.1, U6.3 (+)
unnamed: R85.1, U7.3 (+)
unnamed: R84.2, R93.2, RV7.1, U7.2 (-)
unnamed: R86.2, U7.5 (+)
OUT+: J1.2, J2.5
OUT-: J1.4, J2.6
OUT-A: J2.11, R28.1, R29.1, RV8.1, U2.1, U5.5 (+)
PAD: C5.1, R8.1, RV1.2, RV1.3
PGND: J1.13, R48.1
RATIO_CW: J2.19, R44.1, U4.1
RATIO_W: J2.20, R45.1
REL_W: J2.25, R47.1
SIG-VCA: C11.2, J2.13, R23.2, U1.7, U2.3 (+)
STA: Q6.2 (B), Q8.2 (B), U6.1, U6.2 (-)
STB: Q7.2 (B), Q9.2 (B), R68.2, R69.1
THR_W: J2.18, R35.1
TIMING: C15.1, D7.2 (A), J2.24, U4.5 (+)
VBIAS: C6.1, C7.1, R9.1, R10.1, R11.2, R12.2

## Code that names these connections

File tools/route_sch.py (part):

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The approach is the one a human drafter uses, not "route everything":

  * Rails (+16V / -16V / -5V1) become power symbols at each pin.
  * Grounds (AGND / PGND / CHASSIS) become ground symbols at each pin.
  * Any net with more pins than MAX_FANOUT stays a named label - drawing 14
    wires to one node makes a schematic less readable, not more.
  * Everything left - the local signal nets - is drawn as orthogonal wire.
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        pts = [place_pin(v[0], v[1], part.X, part.Y, part.rot) for v in pins.values()]
        gx = [int(round(x / GRID)) for x, _ in pts]
        gy = [int(round(y / GRID)) for _, y in pts]
        pad = 1
        for x in range(min(gx) - pad, max(gx) + pad + 1):
            for y in range(min(gy) - pad, max(gy) + pad + 1):
                self.blocked.add((x, y))
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
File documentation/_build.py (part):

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    <button class="iv-tab on" data-view="schematic">Schematic</button>
    <button class="iv-tab" data-view="graph">Connections</button>
    <span class="iv-sp"></span>
    <input class="iv-find" type="search" placeholder="find R14, VBIAS…" aria-label="Find part or net">
    <button class="iv-btn iv-zout" title="Zoom out">&minus;</button>
    <button class="iv-btn iv-zin" title="Zoom in">+</button>
    <button class="iv-btn iv-lay" title="Change graph layout">Flow</button>
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<ul>
  <li><strong>Audio ground (pin 5)</strong> is the reference every signal voltage is measured against.</li>
  <li><strong>PSU ground (pin 13)</strong> is the return path for supply current, which is noisy.</li>
  <li><strong>Chassis ground (pin 1)</strong> is metalwork and shielding.</li>
</ul>
<p>They are joined at exactly one point on the module &mdash; a single 0 &Omega; link,
<code>R48</code>, on the power sheet. Joining them at more than one point creates a loop that
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circuit, not just "gain set to unity". That is what makes an A/B comparison trustworthy.</p>

<h2>The aux section</h2>
<p>Drawn as a separable block because it uses chassis-specific pins:</p>
<ul>
  <li><strong>Aux in (pins 11, 9)</strong> &rarr; <code>U5A</code>, another difference amplifier,
      producing the <code>KEY</code> net. This is an <em>external key</em> input: it lets the
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     ["Bypass", "SW1", "Hard bypass &mdash; audio goes straight through the rack."],
     ["Key int/ext", "SW2", "Detector listens to this channel, or to the aux input."],
     ["HPF defeat", "SW3", "Shorts out the 72 Hz detector filter."],
     ["Link", "SW4", "Ties this detector to the other module on pin 6."]],
    ["", "r", ""]) + """

<div class="note">
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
